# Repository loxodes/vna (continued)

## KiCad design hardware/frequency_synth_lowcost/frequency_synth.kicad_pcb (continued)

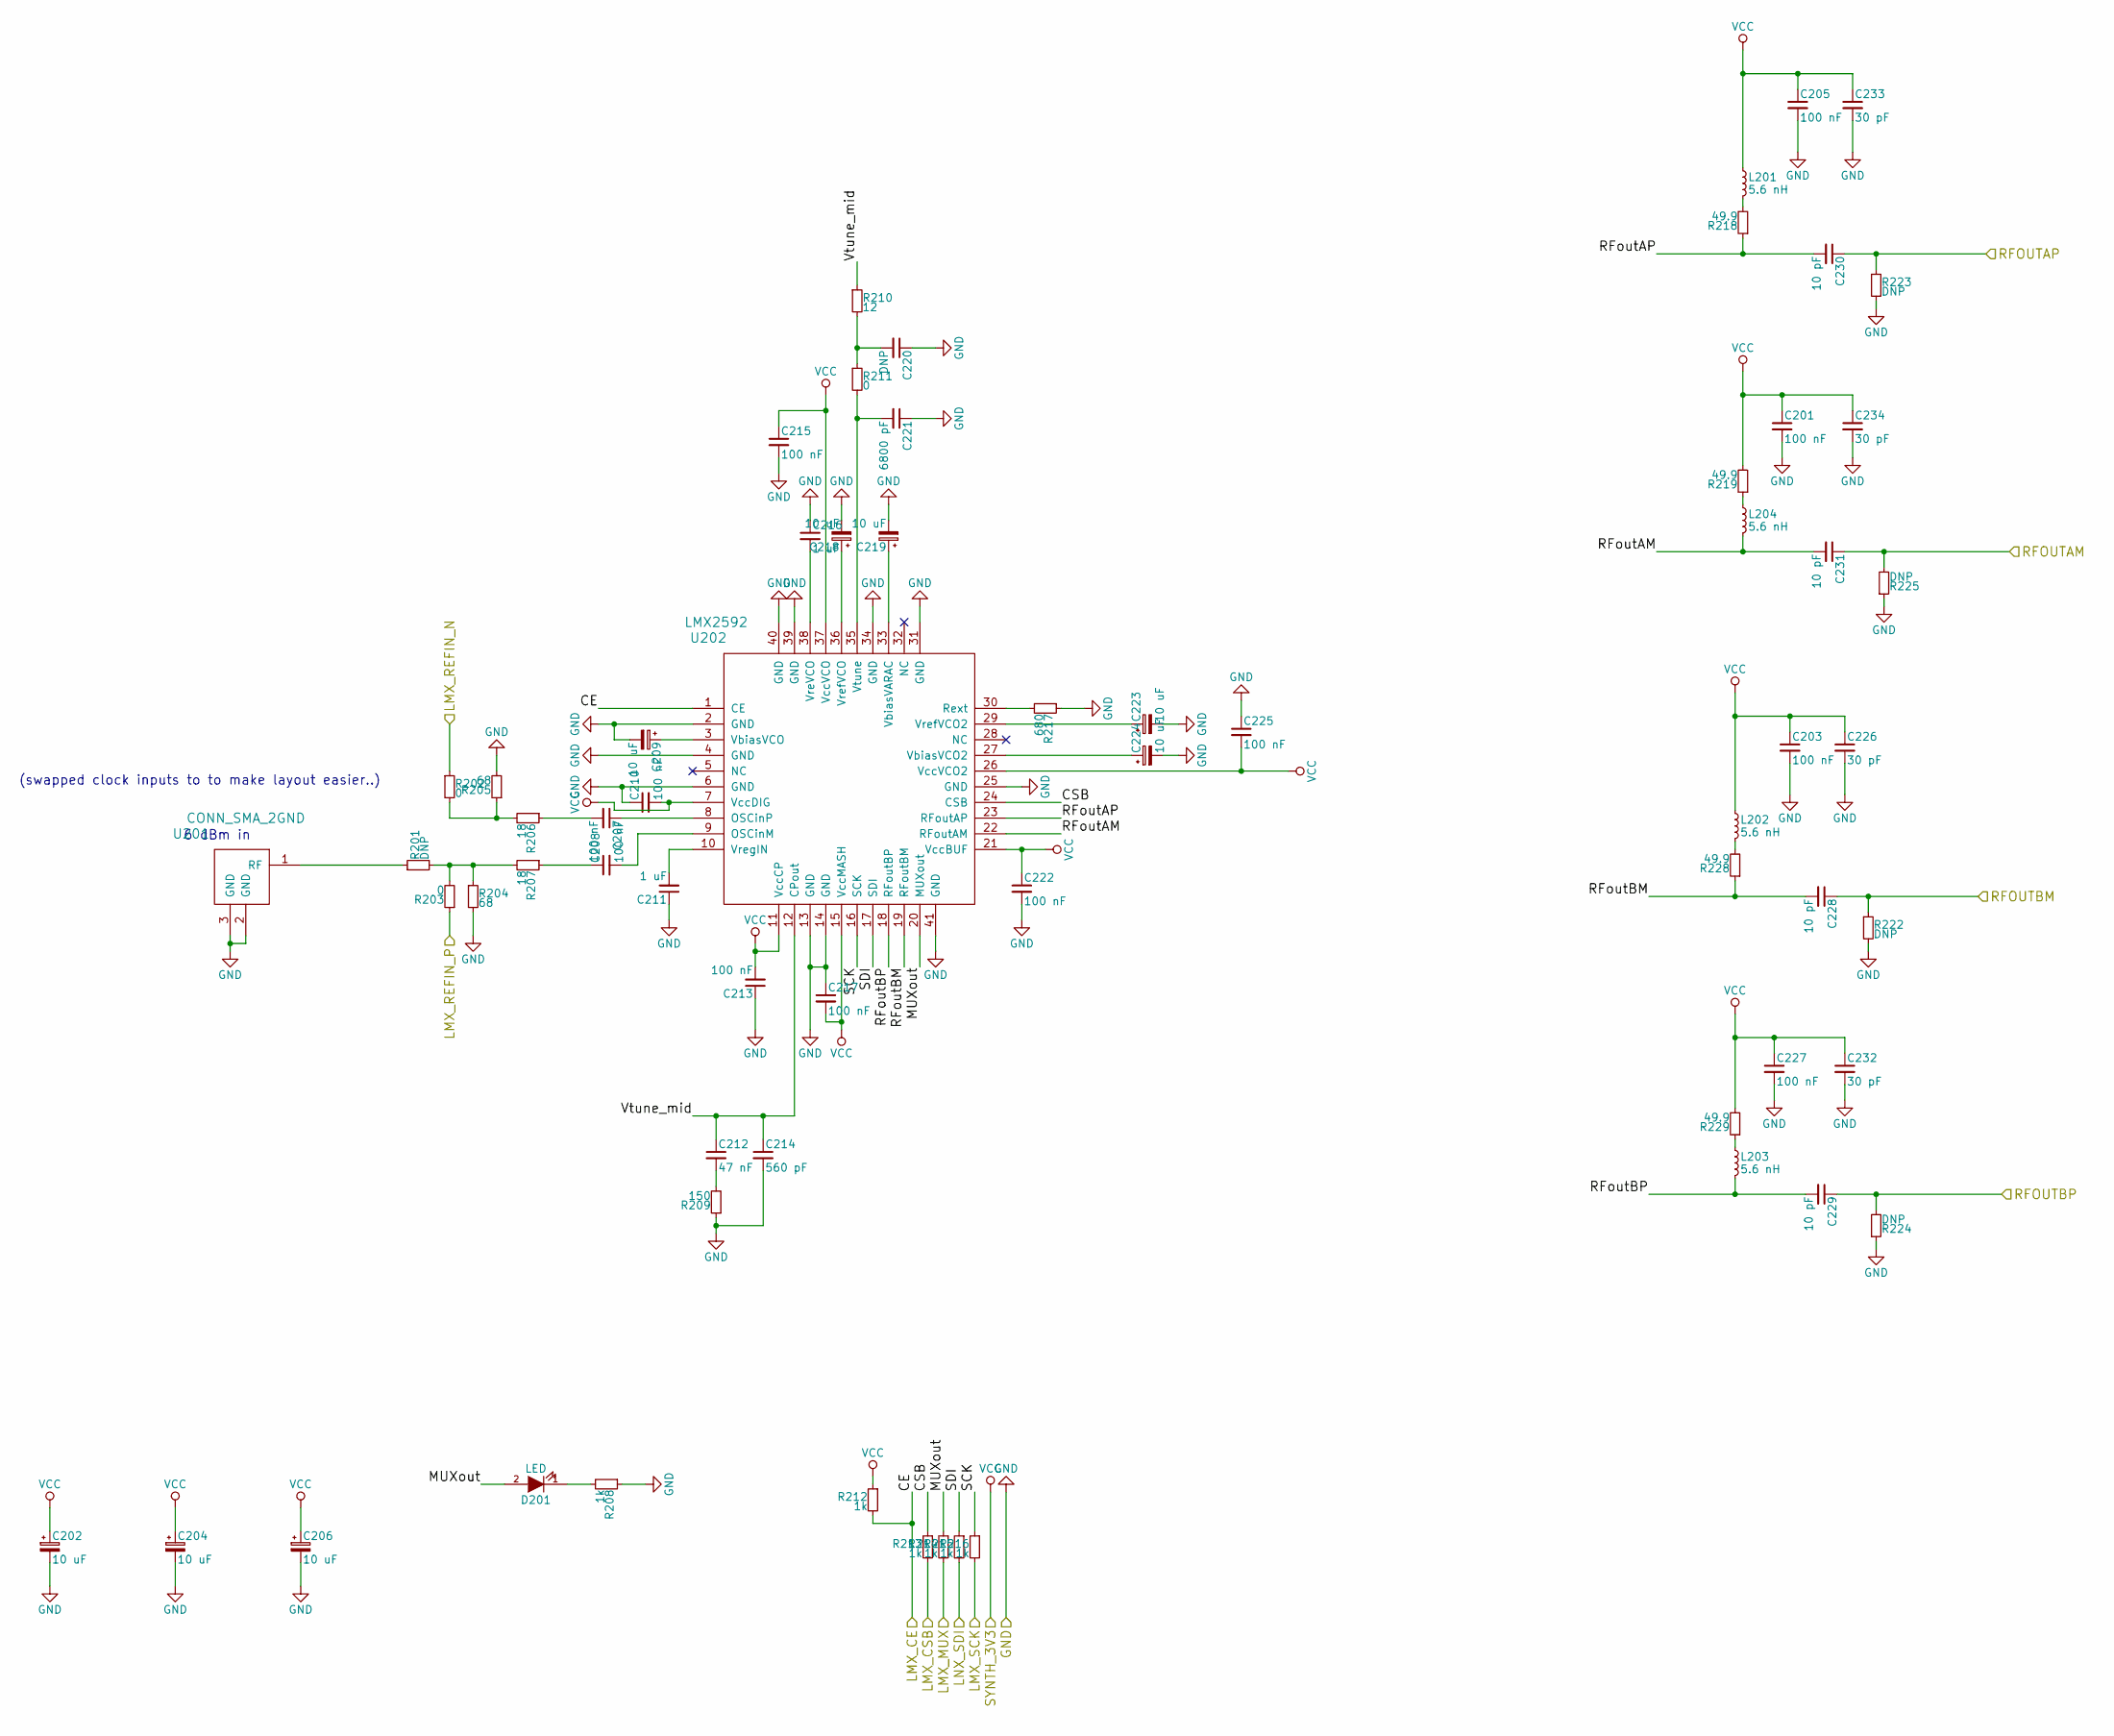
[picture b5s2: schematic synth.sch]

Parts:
C201, C203, C205, C207, C208, C210, C213, C215, C217, C222, C225, C227: 100 nF; C_0402
C202, C204, C206, C209, C218, C219, C223, C224: 10 uF; C_0603
C211, C216: 1 uF; C_0402
C212: 47 nF; C_0402
C214: 560 pF; C_0402
C220: DNP; C_0402
C221: 6800 pF; C_0402
C226, C232, C233, C234: 30 pF; C_0402
C228, C229, C230, C231: 10 pF; C_0402
D201: LED; LED_0603
L201, L202, L203, L204: 5.6 nH; R_0402
R201, R222, R223, R224, R225: DNP; R_0402
R202, R203, R211: 0; R_0402
R204, R205: 68; R_0402
R206, R207: 18; R_0402
R208, R212, R213, R214, R215, R216: 1k; R_0402
R209: 150; R_0402
R210: 12; R_0402
R217: 680; R_0402
R218, R219, R228, R229: 49.9; R_0402
U201: CONN_SMA_2GND; 734120110_ufl_umc
U202: LMX2592; QFN-40-1EP_6x6mm_Pitch0.5mm

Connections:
+3V3: C201.1, C202.1, C203.1, C204.1, C205.1, C206.1, C210.2, C213.2, C215.1, C217.2, C222.1, C225.2, C226.1, C227.1, C232.1, C233.1, C234.1, L201.1, L202.1, R212.1, R219.2, R229.2, U202.7 (VccDIG), U202.11 (VccCP), U202.15 (VccMASH), U202.21 (VccBUF), U202.26 (VccVCO2), U202.37 (VccVCO); also elsewhere on the board
/LMX_CE: R212.2, U202.1 (CE); also elsewhere on the board
/LMX_CSB: R213.2; also elsewhere on the board
/LMX_MUX: R214.2; also elsewhere on the board
/LMX_SCK: R216.2; also elsewhere on the board
/LMX_SDI: R215.2; also elsewhere on the board
/filter bank/RFINA: C229.1, C229.2, L203.2, R224.2, U202.18 (RFoutBP); also elsewhere on the board
/filter bank/RFINB: C228.1, C228.2, R222.1, R228.1, U202.19 (RFoutBM); also elsewhere on the board
/filter bank/RFINC: C231.1, C231.2, L204.2, R225.2, U202.22 (RFoutAM); also elsewhere on the board
/filter bank/RFIND: C230.1, C230.2, R218.1, R223.1, U202.23 (RFoutAP); also elsewhere on the board
/frequency_synth/CSB: R213.1, U202.24 (CSB)
/frequency_synth/LMX_REFIN_N: R202.1; also elsewhere on the board
/frequency_synth/LMX_REFIN_P: R203.1; also elsewhere on the board
/frequency_synth/MUXout: D201.2 (A), R214.1, U202.20 (MUXout)
/frequency_synth/SCK: R216.1, U202.16 (SCK)
/frequency_synth/SDI: R215.1, U202.17 (SDI)
/frequency_synth/Vtune_mid: C212.1, C214.1, R210.1, U202.12 (CPout)
GND: C201.2, C202.2, C203.2, C204.2, C205.2, C206.2, C209.2, C210.1, C211.1, C213.1, C214.2, C215.2, C216.1, C217.1, C218.2, C219.2, C220.1, C221.1, C222.2, C223.2, C224.2, C225.1, C226.2, C227.2, C232.2, C233.2, C234.2, R204.2, R205.2, R208.1, R209.1, R217.1, R222.2, R223.2, R224.1, R225.1, U201.2 (GND), U201.3 (GND), U202.2 (GND), U202.4 (GND), U202.6 (GND), U202.13 (GND), U202.14 (GND), U202.25 (GND), U202.31 (GND), U202.34 (GND), U202.39 (GND), U202.40 (GND), U202.41 (GND); also elsewhere on the board
unnamed: C207.1, U202.8 (OSCinP)
unnamed: C207.2, R206.1
unnamed: C208.1, R207.1
unnamed: C208.2, U202.9 (OSCinM)
unnamed: C209.1, U202.3 (VbiasVCO)
unnamed: C211.2, U202.10 (VregIN)
unnamed: C212.2, R209.2
unnamed: C216.2, U202.38 (VreVCO)
unnamed: C218.1, U202.36 (VrefVCO)
unnamed: C219.1, U202.33 (VbiasVARAC)
unnamed: C220.2, R210.2, R211.1
unnamed: C221.2, R211.2, U202.35 (Vtune)
unnamed: C223.1, U202.29 (VrefVCO2)
unnamed: C224.1, U202.27 (VbiasVCO2)
unnamed: D201.1 (K), R208.2
unnamed: L201.2, R218.2
unnamed: L202.2, R228.2
unnamed: L203.1, R229.1
unnamed: L204.1, R219.1
unnamed: R201.1, U201.1 (RF)
unnamed: R201.2, R203.2, R204.1, R207.2
unnamed: R202.2, R205.1, R206.2
unnamed: R217.2, U202.30 (Rext)

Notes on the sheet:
6 dBm in
(swapped clock inputs to to make layout easier..)

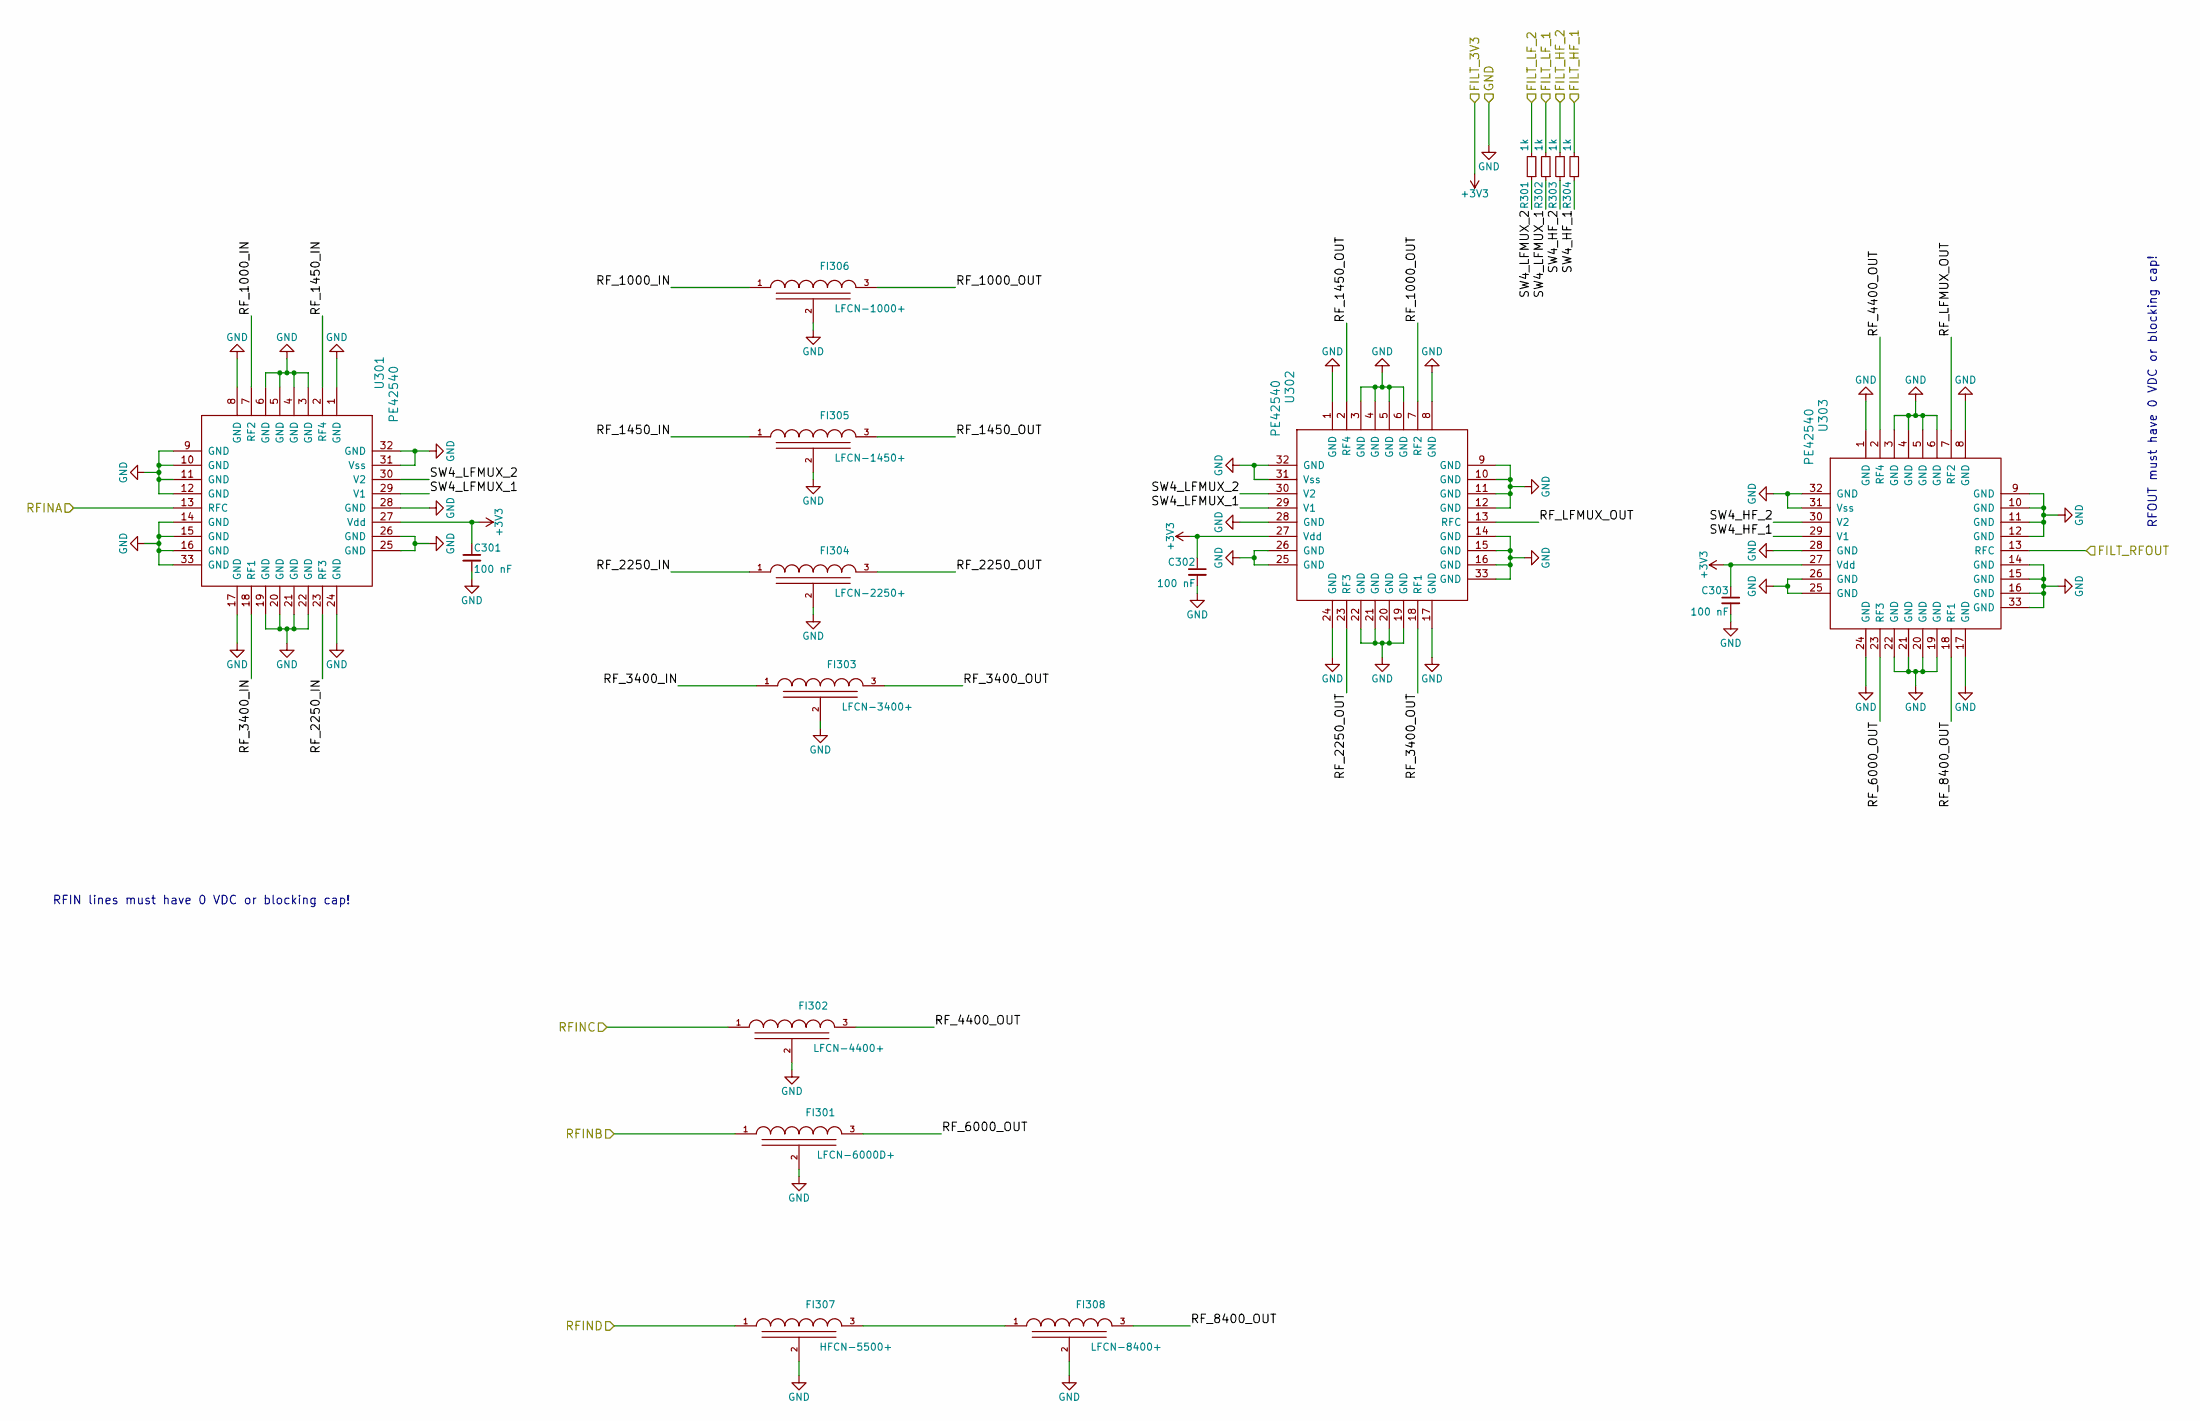
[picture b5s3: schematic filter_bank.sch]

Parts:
C301, C302, C303: 100 nF; C_0402
FI301: LFCN-6000D+; FV1206-narrow
FI302: LFCN-4400+; FV1206-narrow
FI303: LFCN-3400+; FV1206-narrow
FI304: LFCN-2250+; FV1206-narrow
FI305: LFCN-1450+; FV1206-narrow
FI306: LFCN-1000+; FV1206-narrow
FI307: HFCN-5500+; FV1206-1_p35mm_ustrip
FI308: LFCN-8400+; FV1206-4
R301, R302, R303, R304: 1k; R_0402
U301, U302, U303: PE42540; LGA_32

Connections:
+3V3: C301.1, C302.1, C303.1, U301.27 (Vdd), U302.27 (Vdd), U303.27 (Vdd); also elsewhere on the board
/FILT_HF_1: R304.2; also elsewhere on the board
/FILT_HF_2: R303.2; also elsewhere on the board
/FILT_LF_1: R302.2; also elsewhere on the board
/FILT_LF_2: R301.2; also elsewhere on the board
/attenuator/ATT_RFIN: U303.13 (RFC); also elsewhere on the board
/filter bank/RFINA: U301.13 (RFC); also elsewhere on the board
/filter bank/RFINB: FI301.1 (VI); also elsewhere on the board
/filter bank/RFINC: FI302.1 (VI); also elsewhere on the board
/filter bank/RFIND: FI307.1 (VI); also elsewhere on the board
/filter bank/RF_1000_IN: FI306.1 (VI), U301.7 (RF2)
/filter bank/RF_1000_OUT: FI306.3 (VO), U302.7 (RF2)
/filter bank/RF_1450_IN: FI305.1 (VI), U301.2 (RF4)
/filter bank/RF_1450_OUT: FI305.3 (VO), U302.2 (RF4)
/filter bank/RF_2250_IN: FI304.1 (VI), U301.23 (RF3)
/filter bank/RF_2250_OUT: FI304.3 (VO), U302.23 (RF3)
/filter bank/RF_3400_IN: FI303.1 (VI), U301.18 (RF1)
/filter bank/RF_3400_OUT: FI303.3 (VO), U302.18 (RF1)
/filter bank/RF_4400_OUT: FI302.3 (VO), U303.2 (RF4)
/filter bank/RF_6000_OUT: FI301.3 (VO), U303.23 (RF3)
/filter bank/RF_8400_OUT: FI308.3 (VO), U303.18 (RF1)
/filter bank/RF_LFMUX_OUT: U302.13 (RFC), U303.7 (RF2)
/filter bank/SW4_HF_1: R304.1, U303.29 (V1)
/filter bank/SW4_HF_2: R303.1, U303.30 (V2)
/filter bank/SW4_LFMUX_1: R302.1, U301.29 (V1), U302.29 (V1)
/filter bank/SW4_LFMUX_2: R301.1, U301.30 (V2), U302.30 (V2)
GND: C301.2, C302.2, C303.2, FI301.2 (GND), FI302.2 (GND), FI303.2 (GND), FI304.2 (GND), FI305.2 (GND), FI306.2 (GND), FI307.2 (GND), FI308.2 (GND), U301.1 (GND), U301.3 (GND), U301.4 (GND), U301.5 (GND), U301.6 (GND), U301.8 (GND), U301.9 (GND), U301.10 (GND), U301.11 (GND), U301.12 (GND), U301.14 (GND), U301.15 (GND), U301.16 (GND), U301.17 (GND), U301.19 (GND), U301.20 (GND), U301.21 (GND), U301.22 (GND), U301.24 (GND), U301.25 (GND), U301.26 (GND), U301.28 (GND), U301.31 (Vss), U301.32 (GND), U301.33 (GND), U302.1 (GND), U302.3 (GND), U302.4 (GND), U302.5 (GND), U302.6 (GND), U302.8 (GND), U302.9 (GND), U302.10 (GND), U302.11 (GND), U302.12 (GND), U302.14 (GND), U302.15 (GND), U302.16 (GND), U302.17 (GND), U302.19 (GND), U302.20 (GND), U302.21 (GND), U302.22 (GND), U302.24 (GND), U302.25 (GND), U302.26 (GND), U302.28 (GND), U302.31 (Vss), U302.32 (GND), U302.33 (GND), U303.1 (GND), U303.3 (GND), U303.4 (GND), U303.5 (GND), U303.6 (GND), U303.8 (GND), U303.9 (GND), U303.10 (GND), U303.11 (GND), U303.12 (GND), U303.14 (GND), U303.15 (GND), U303.16 (GND), U303.17 (GND), U303.19 (GND), U303.20 (GND), U303.21 (GND), U303.22 (GND), U303.24 (GND), U303.25 (GND), U303.26 (GND), U303.28 (GND), U303.31 (Vss), U303.32 (GND), U303.33 (GND); also elsewhere on the board
unnamed: FI307.3 (VO), FI308.1 (VI)

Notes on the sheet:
RFOUT must have 0 VDC or blocking cap!
RFIN lines must have 0 VDC or blocking cap!

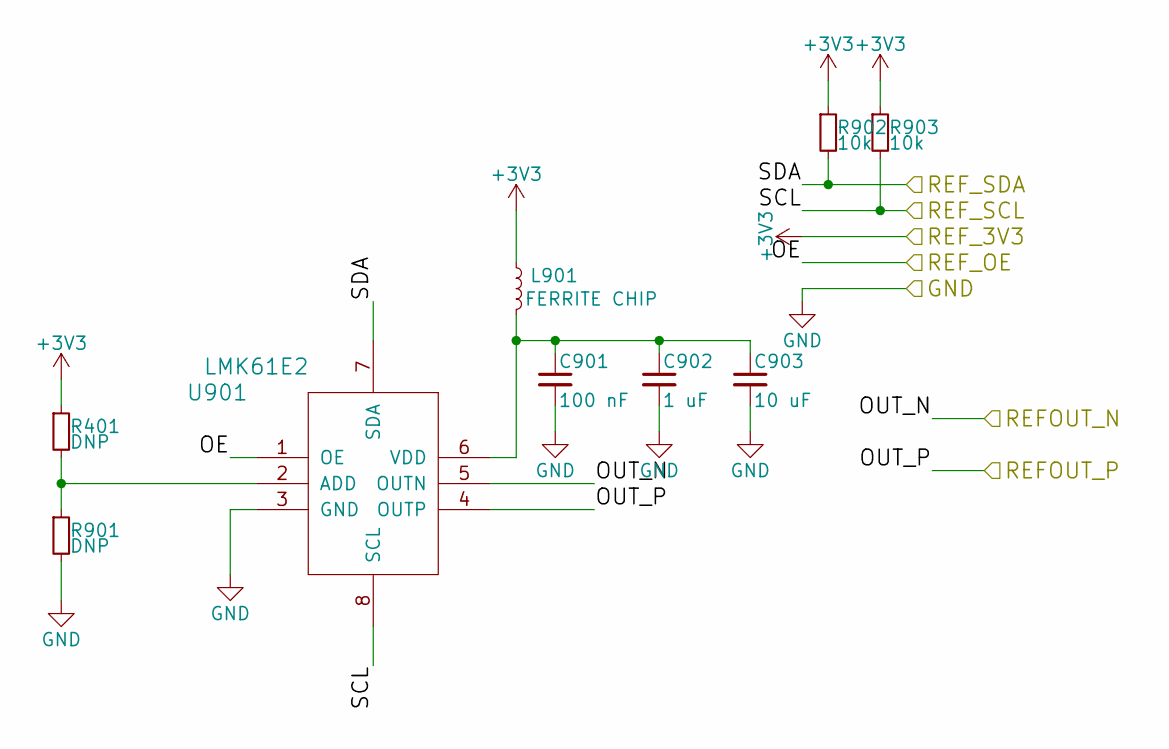
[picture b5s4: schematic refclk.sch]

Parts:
C901: 100 nF; C_0402
C902: 1 uF; C_0402
C903: 10 uF; C_0603
L901: FERRITE CHIP; R_0603
R401, R901: DNP; R_0402
R902, R903: 10k; R_0402
U901: LMK61E2; QFM8

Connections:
+3V3: L901.1, R401.1, R902.1, R903.1; also elsewhere on the board
/REF_OE: U901.1 (OE); also elsewhere on the board
/REF_SCL: R903.2, U901.8 (SCL); also elsewhere on the board
/REF_SDA: R902.2, U901.7 (SDA); also elsewhere on the board
/frequency_synth/LMX_REFIN_N: U901.5 (OUTN); also elsewhere on the board
/frequency_synth/LMX_REFIN_P: U901.4 (OUTP); also elsewhere on the board
GND: C901.2, C902.2, C903.2, R901.2, U901.3 (GND); also elsewhere on the board
unnamed: C901.1, C902.1, C903.1, L901.2, U901.6 (VDD)
unnamed: R401.2, R901.1, U901.2 (ADD)

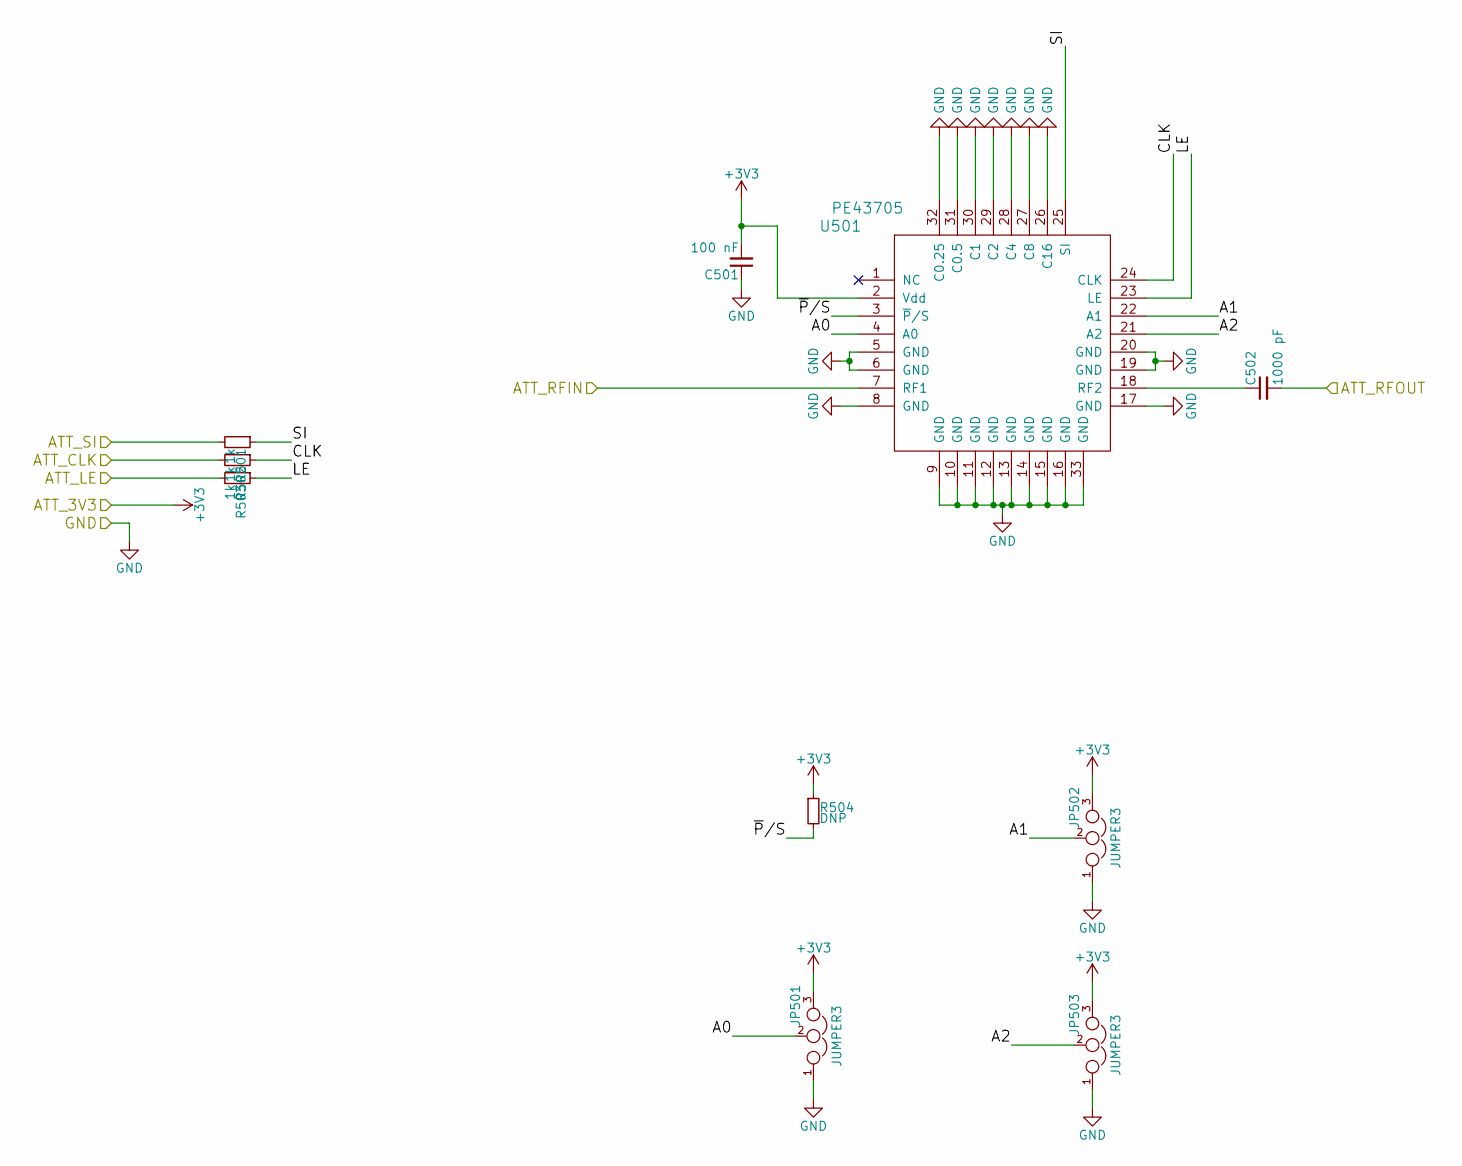
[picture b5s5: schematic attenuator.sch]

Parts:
C501: 100 nF; C_0402
C502: 1000 pF; C_0402
JP501, JP502, JP503: JUMPER3; JMP_3
R501, R502, R503: 1k; R_0402
R504: DNP; R_0402
U501: PE43705; QFN-32-1EP_5x5mm_PE_Pitch0.5mm

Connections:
+3V3: C501.2, JP501.3, JP502.3, JP503.3, R504.1, U501.2 (Vdd); also elsewhere on the board
/ATT_CLK: R502.2; also elsewhere on the board
/ATT_LE: R503.2; also elsewhere on the board
/ATT_SI: R501.2; also elsewhere on the board
/attenuator/A0: JP501.2, U501.4 (A0)
/attenuator/A1: JP502.2, U501.22 (A1)
/attenuator/A2: JP503.2, U501.21 (A2)
/attenuator/ATT_RFIN: U501.7 (RF1); also elsewhere on the board
/attenuator/ATT_RFOUT: C502.2; also elsewhere on the board
/attenuator/CLK: R502.1, U501.24 (CLK)
/attenuator/LE: R503.1, U501.23 (LE)
/attenuator/SI: R501.1, U501.25 (SI)
/attenuator/~P~/S: R504.2, U501.3 (~P~/S)
GND: C501.1, JP501.1, JP502.1, JP503.1, U501.5 (GND), U501.6 (GND), U501.8 (GND), U501.9 (GND), U501.10 (GND), U501.11 (GND), U501.12 (GND), U501.13 (GND), U501.14 (GND), U501.15 (GND), U501.16 (GND), U501.17 (GND), U501.19 (GND), U501.20 (GND), U501.26 (C16), U501.27 (C8), U501.28 (C4), U501.29 (C2), U501.30 (C1), U501.31 (C0.5), U501.32 (C0.25), U501.33 (GND); also elsewhere on the board
unnamed: C502.1, U501.18 (RF2)

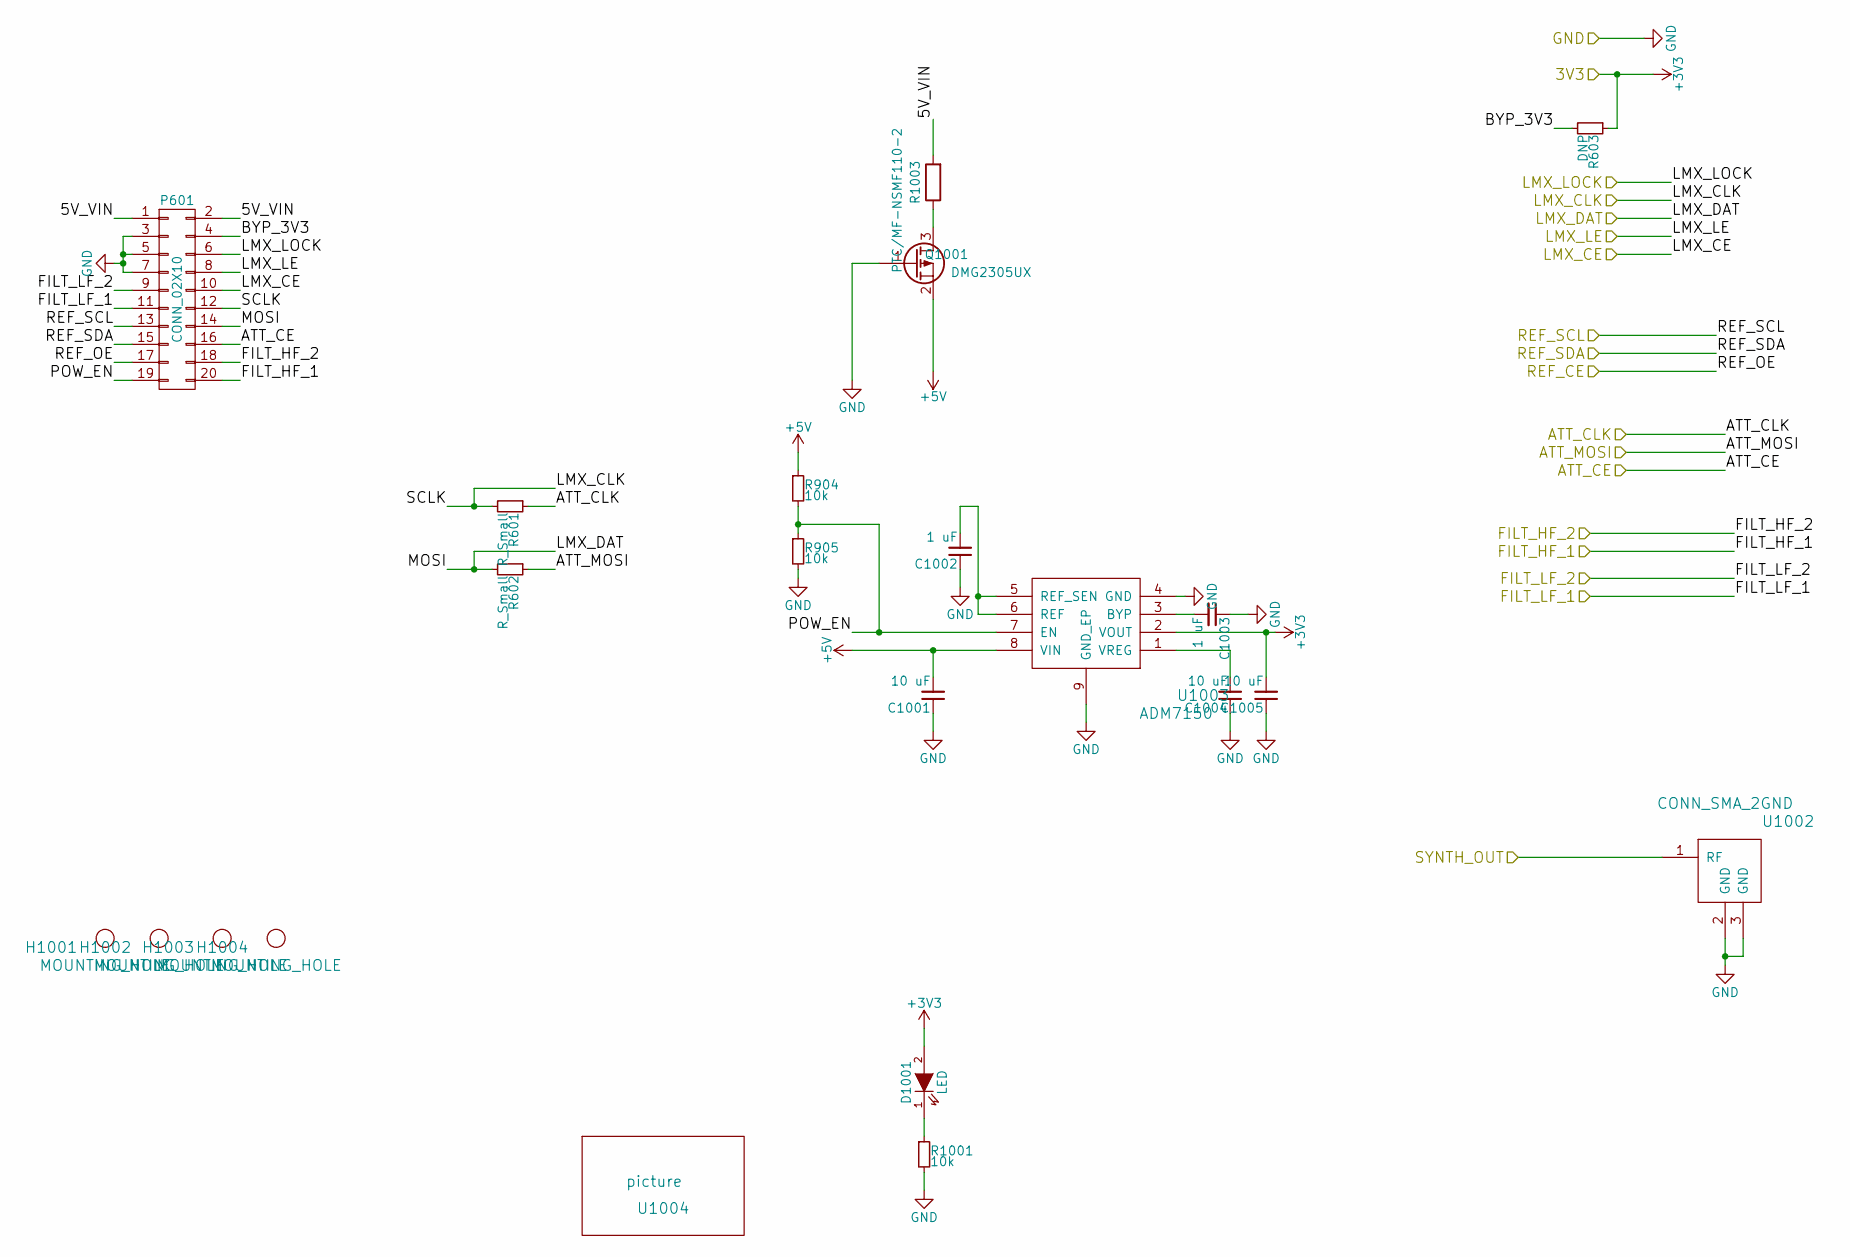
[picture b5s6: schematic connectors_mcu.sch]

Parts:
C1001, C1004, C1005: 10 uF; C_0603
C1002, C1003: 1 uF; C_0402
D1001: LED; LED_0603
H1001, H1002, H1003, H1004: MOUNTING_HOLE; MountingHole_2-7mm
P601: CONN_02X10; IDC_Header_Straight_20pins
Q1001: DMG2305UX; SOT-23
R601, R602: R_Small; R_0402
R603: DNP; R_0402
R904, R905, R1001: 10k; R_0402
R1003: PTC/MF-NSMF110-2; R_1206
U1002: CONN_SMA_2GND; SMA_CPW_1MM_.2MM
U1003: ADM7150; DFN-8-1EP_3x3mm_Pitch0.5mm
U1004: picture; cat

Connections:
+3V3: C1005.2, D1001.2 (A), R603.1, U1003.2 (VOUT); also elsewhere on the board
+5V: C1001.2, Q1001.2 (S), R904.1, U1003.8 (VIN)
/ATT_CLK: R601.1; also elsewhere on the board
/ATT_LE: P601.16; also elsewhere on the board
/ATT_SI: R602.1; also elsewhere on the board
/FILT_HF_1: P601.20; also elsewhere on the board
/FILT_HF_2: P601.18; also elsewhere on the board
/FILT_LF_1: P601.11; also elsewhere on the board
/FILT_LF_2: P601.9; also elsewhere on the board
/LMX_CE: P601.10; also elsewhere on the board
/LMX_CSB: P601.8; also elsewhere on the board
/LMX_MUX: P601.6; also elsewhere on the board
/LMX_SCK: P601.12, R601.2; also elsewhere on the board
/LMX_SDI: P601.14, R602.2; also elsewhere on the board
/REF_OE: P601.17; also elsewhere on the board
/REF_SCL: P601.13; also elsewhere on the board
/REF_SDA: P601.15; also elsewhere on the board
/attenuator/ATT_RFOUT: U1002.1 (RF); also elsewhere on the board
/connectors, microcontroller, psu/5V_VIN: P601.1, P601.2, R1003.2
/connectors, microcontroller, psu/BYP_3V3: P601.4, R603.2
/connectors, microcontroller, psu/POW_EN: P601.19, R904.2, R905.1, U1003.7 (EN)
GND: C1001.1, C1002.1, C1003.1, C1004.1, C1005.1, P601.3, P601.5, P601.7, Q1001.1 (G), R905.2, R1001.2, U1002.2 (GND), U1002.3 (GND), U1003.4 (GND), U1003.9 (GND_EP); also elsewhere on the board
unnamed: C1002.2, U1003.5 (REF_SEN), U1003.6 (REF)
unnamed: C1003.2, U1003.3 (BYP)
unnamed: C1004.2, U1003.1 (VREG)
unnamed: D1001.1 (K), R1001.1
unnamed: Q1001.3 (D), R1003.1

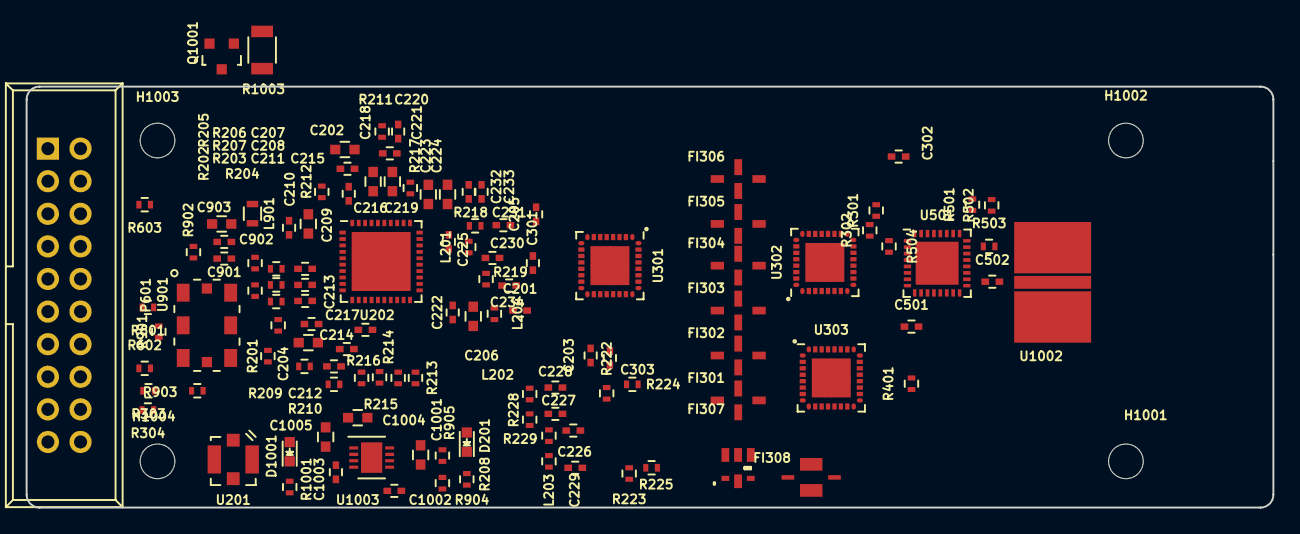
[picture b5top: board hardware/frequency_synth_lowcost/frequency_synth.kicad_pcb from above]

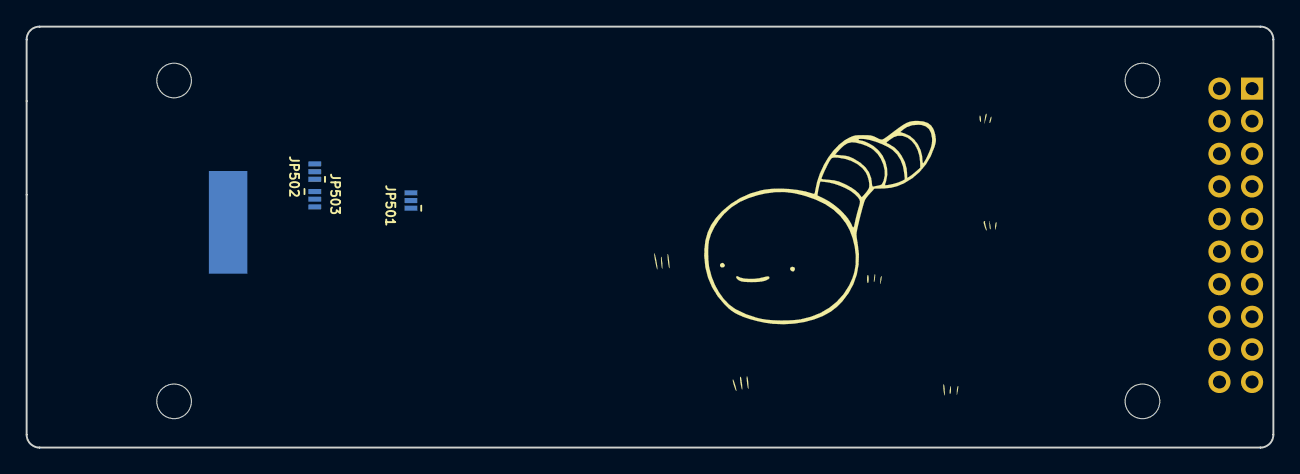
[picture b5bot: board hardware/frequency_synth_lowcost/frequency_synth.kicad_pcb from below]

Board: 4 copper layers, 97.1 x 32.8 mm, 125 parts (4 on the bottom side), 89 nets.

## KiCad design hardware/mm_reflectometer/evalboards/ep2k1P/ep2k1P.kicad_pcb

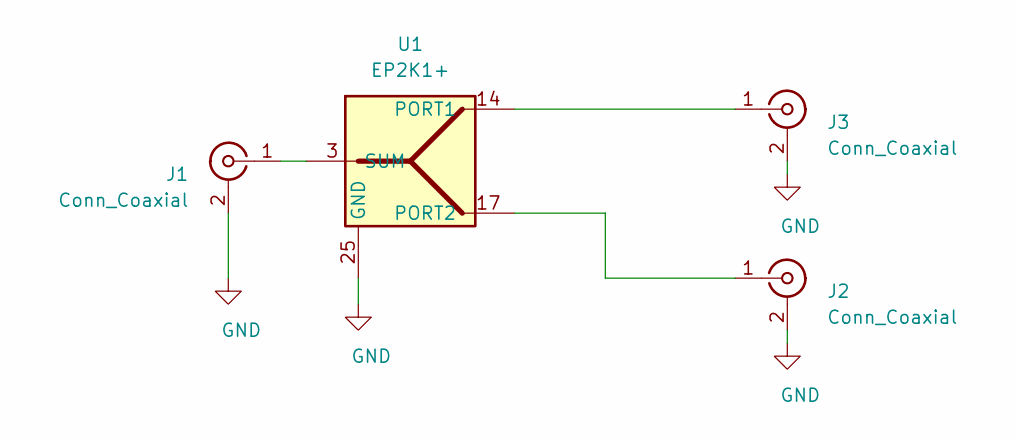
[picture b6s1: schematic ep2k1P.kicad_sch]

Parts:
J1, J2, J3: Conn_Coaxial; sw_edge_oshpark_4layer
U1: EP2K1+; DG1847; mpn EP2K1+; mouser# 139-EP2K1

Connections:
GND: J1.2 (Ext), J2.2 (Ext), J3.2 (Ext), U1.1 (NC), U1.2 (NC), U1.4 (NC), U1.5 (NC), U1.6 (NC), U1.7 (NC), U1.8 (NC), U1.9 (NC), U1.10 (NC), U1.11 (NC), U1.12 (NC), U1.13 (NC), U1.15 (NC), U1.16 (NC), U1.18 (NC), U1.19 (NC), U1.20 (NC), U1.21 (NC), U1.22 (NC), U1.23 (NC), U1.24 (NC), U1.25 (GND)
unnamed: J1.1 (In), U1.3 (SUM)
unnamed: J3.1 (In), U1.14 (PORT1)
unnamed: J2.1 (In), U1.17 (PORT2)

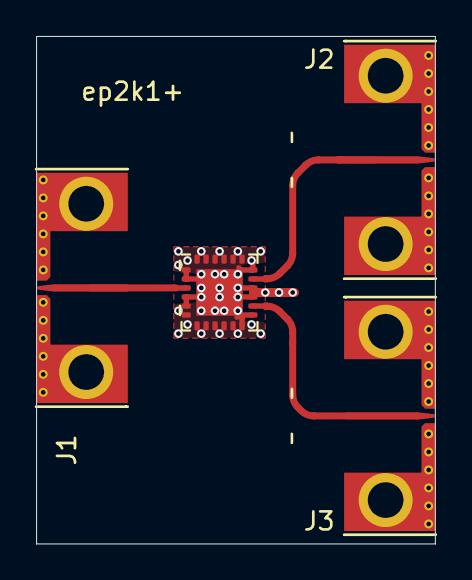
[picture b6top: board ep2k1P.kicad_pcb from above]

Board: 4 copper layers, 22.2 x 28.2 mm, 4 parts (0 on the bottom side), 4 nets.

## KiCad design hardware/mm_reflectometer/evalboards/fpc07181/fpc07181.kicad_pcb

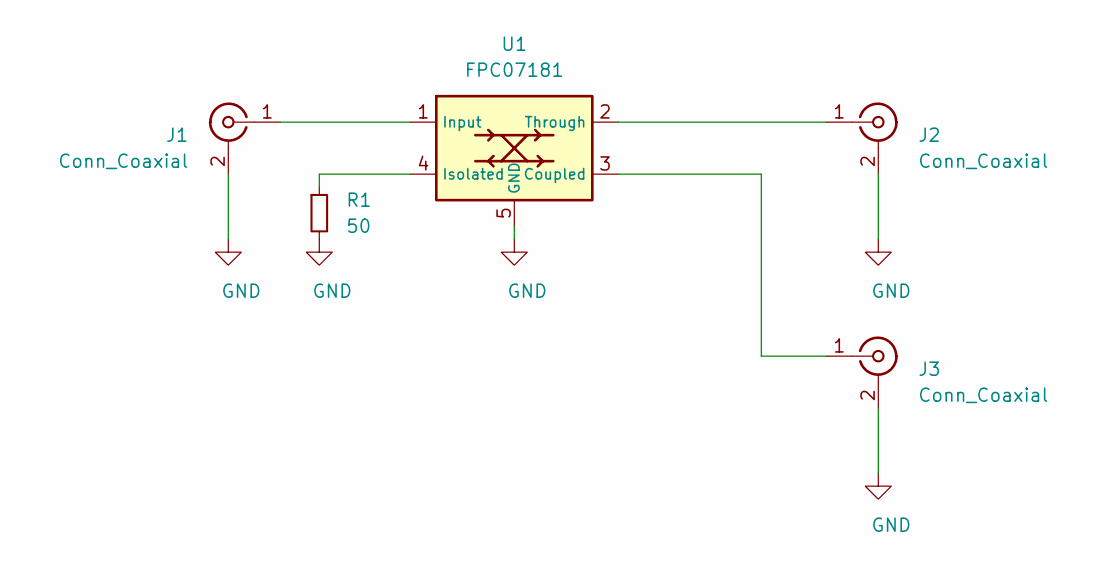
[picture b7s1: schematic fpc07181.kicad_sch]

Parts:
J1, J2, J3: Conn_Coaxial; sw_edge_oshpark_4layer
R1: 50; R_0402_1005Metric
U1: FPC07181; mpn FPC07181; digikey# 1761-1032-ND

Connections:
GND: J1.2 (Ext), J2.2 (Ext), J3.2 (Ext), R1.2, U1.5 (GND)
unnamed: J1.1 (In), U1.1 (Input)
unnamed: J2.1 (In), U1.2 (Through)
unnamed: J3.1 (In), U1.3 (Coupled)
unnamed: R1.1, U1.4 (Isolated)

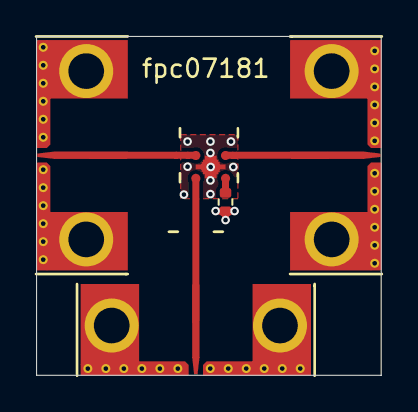
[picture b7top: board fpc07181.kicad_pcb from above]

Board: 4 copper layers, 19.2 x 18.8 mm, 5 parts (0 on the bottom side), 5 nets.
